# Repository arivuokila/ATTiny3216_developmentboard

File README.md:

# ATTiny3216_development board

A simple ATTiny3216 development board made with Kicad 6.0.

The board can be easily programmed with UPDI programmer such as this one: https://gitlab.fabcloud.org/pub/programmers/programmer-updi-d11c

Arduino IDE if using [megaTinyCore](https://github.com/SpenceKonde/megaTinyCore). 

Select from Tools:

Board: ATTiny3216

Port: the SAMD11C14's serial port.

Programmer: SerialUPDI - SLOW

First burn the bootloader and then you are able to upload programs to it. Settings remain the same for both.

[Pinout](https://github.com/SpenceKonde/megaTinyCore/blob/master/megaavr/extras/ATtiny_x16.md) from SpenceKonde's repo. You can find more details related to ATTiny3216 behind that link.

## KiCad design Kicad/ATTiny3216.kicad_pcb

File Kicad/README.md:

Kicad 6.0 files

The schematics of the design is presented in the image below

The design of the board is presented in the image below

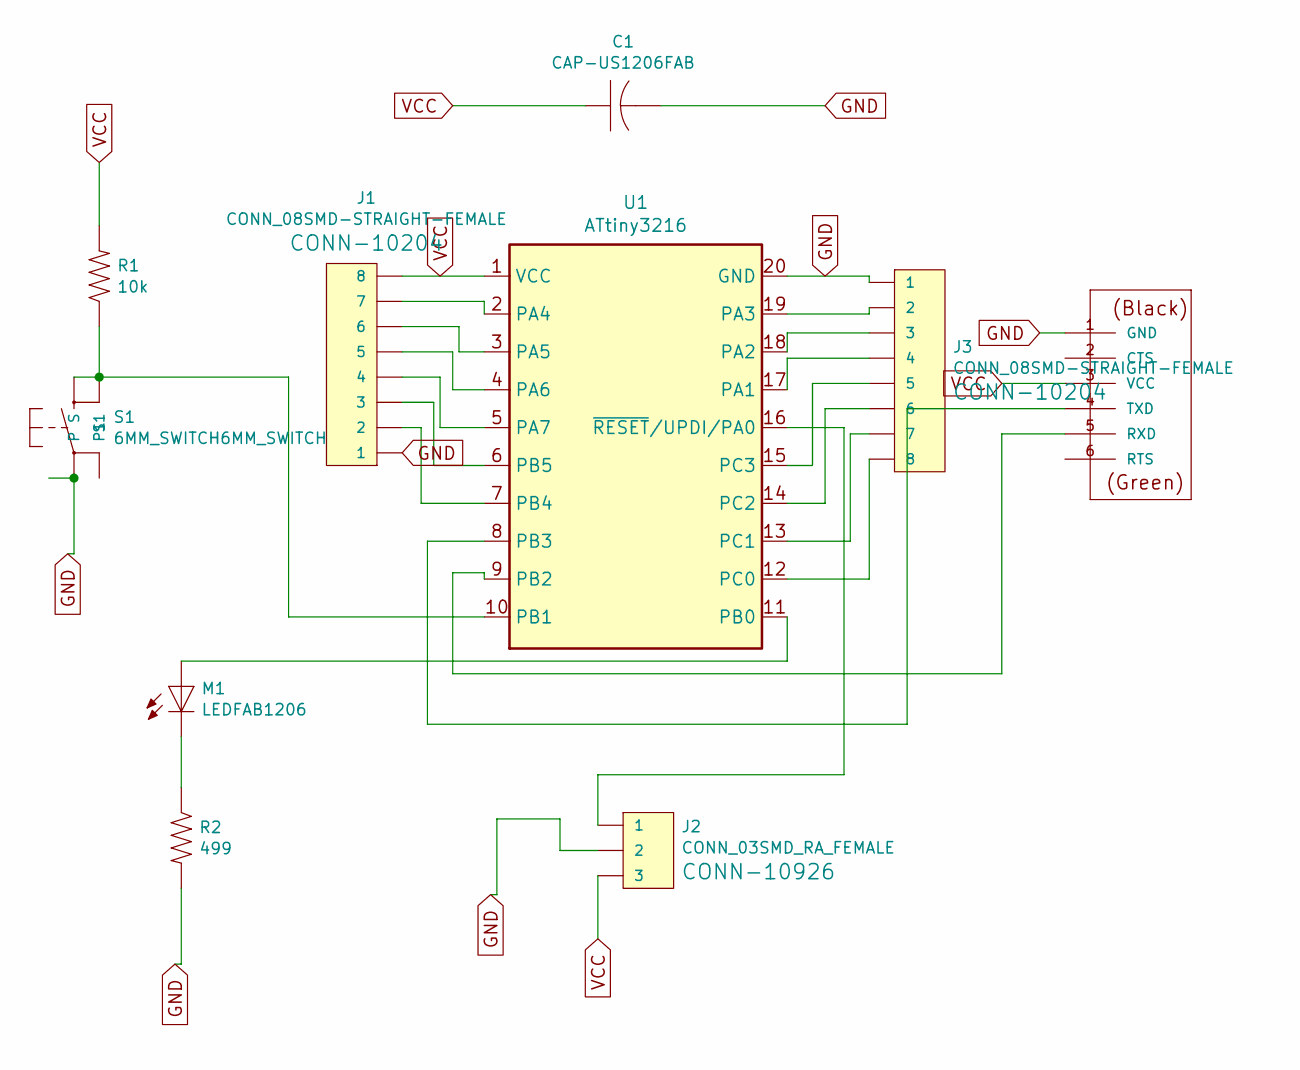
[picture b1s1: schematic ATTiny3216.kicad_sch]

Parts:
C1: CAP-US1206FAB; fab-C1206FAB
J1, J3: CONN_08SMD-STRAIGHT-FEMALE; 1X08_SMD
J2: CONN_03SMD_RA_FEMALE; 1X03_SMD_RA_FEMALE
M1: LEDFAB1206; fab-LED1206FAB
M2: FTDI-SMD-HEADER; fab-1X06SMD
R1: 10k; fab-R1206FAB
R2: 499; fab-R1206FAB
S1: 6MM_SWITCH6MM_SWITCH; fab-6MM_SWITCH
U1: ATtiny3216; fab-SOIC-20_7.5x12.8mm_P1.27mm

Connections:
GND: C1.2, J1.1, J2.2, J3.1, M2.1 (GND), R2.2, S1.1, U1.20 (GND)
unnamed: J1.2, U1.7 (PB4)
unnamed: J1.3, U1.6 (PB5)
unnamed: J1.4, U1.5 (PA7)
unnamed: J1.5, U1.4 (PA6)
unnamed: J1.6, U1.3 (PA5)
unnamed: J1.7, U1.2 (PA4)
unnamed: J2.1, U1.16 (~RESET/UPDI/PA0)
unnamed: J3.2, U1.19 (PA3)
unnamed: J3.3, U1.18 (PA2)
unnamed: J3.4, U1.17 (PA1)
unnamed: J3.5, U1.15 (PC3)
unnamed: J3.6, U1.14 (PC2)
unnamed: J3.7, U1.13 (PC1)
unnamed: J3.8, U1.12 (PC0)
unnamed: M1.1 (A), U1.11 (PB0)
unnamed: M1.2 (C), R2.1
unnamed: M2.4 (TXD), U1.8 (PB3)
unnamed: M2.5 (RXD), U1.9 (PB2)
unnamed: R1.1, S1.3 (S), S1.4 (S1), U1.10 (PB1)
VCC: C1.1, J1.8, J2.3, M2.3 (VCC), R1.2, U1.1 (VCC)

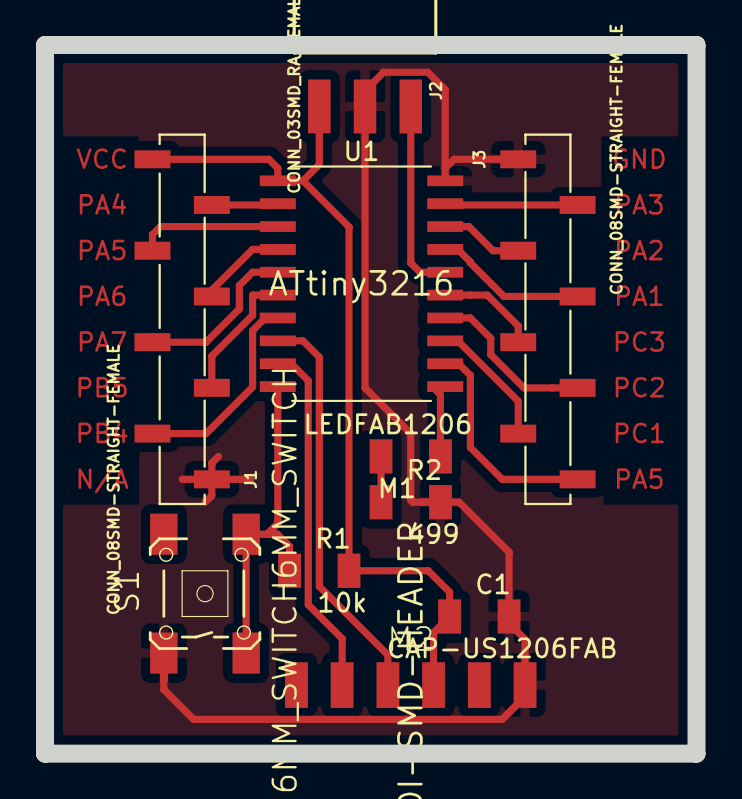
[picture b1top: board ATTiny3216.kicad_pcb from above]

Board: 2 copper layers, 36.2 x 39.4 mm, 10 parts (0 on the bottom side), 21 nets.
